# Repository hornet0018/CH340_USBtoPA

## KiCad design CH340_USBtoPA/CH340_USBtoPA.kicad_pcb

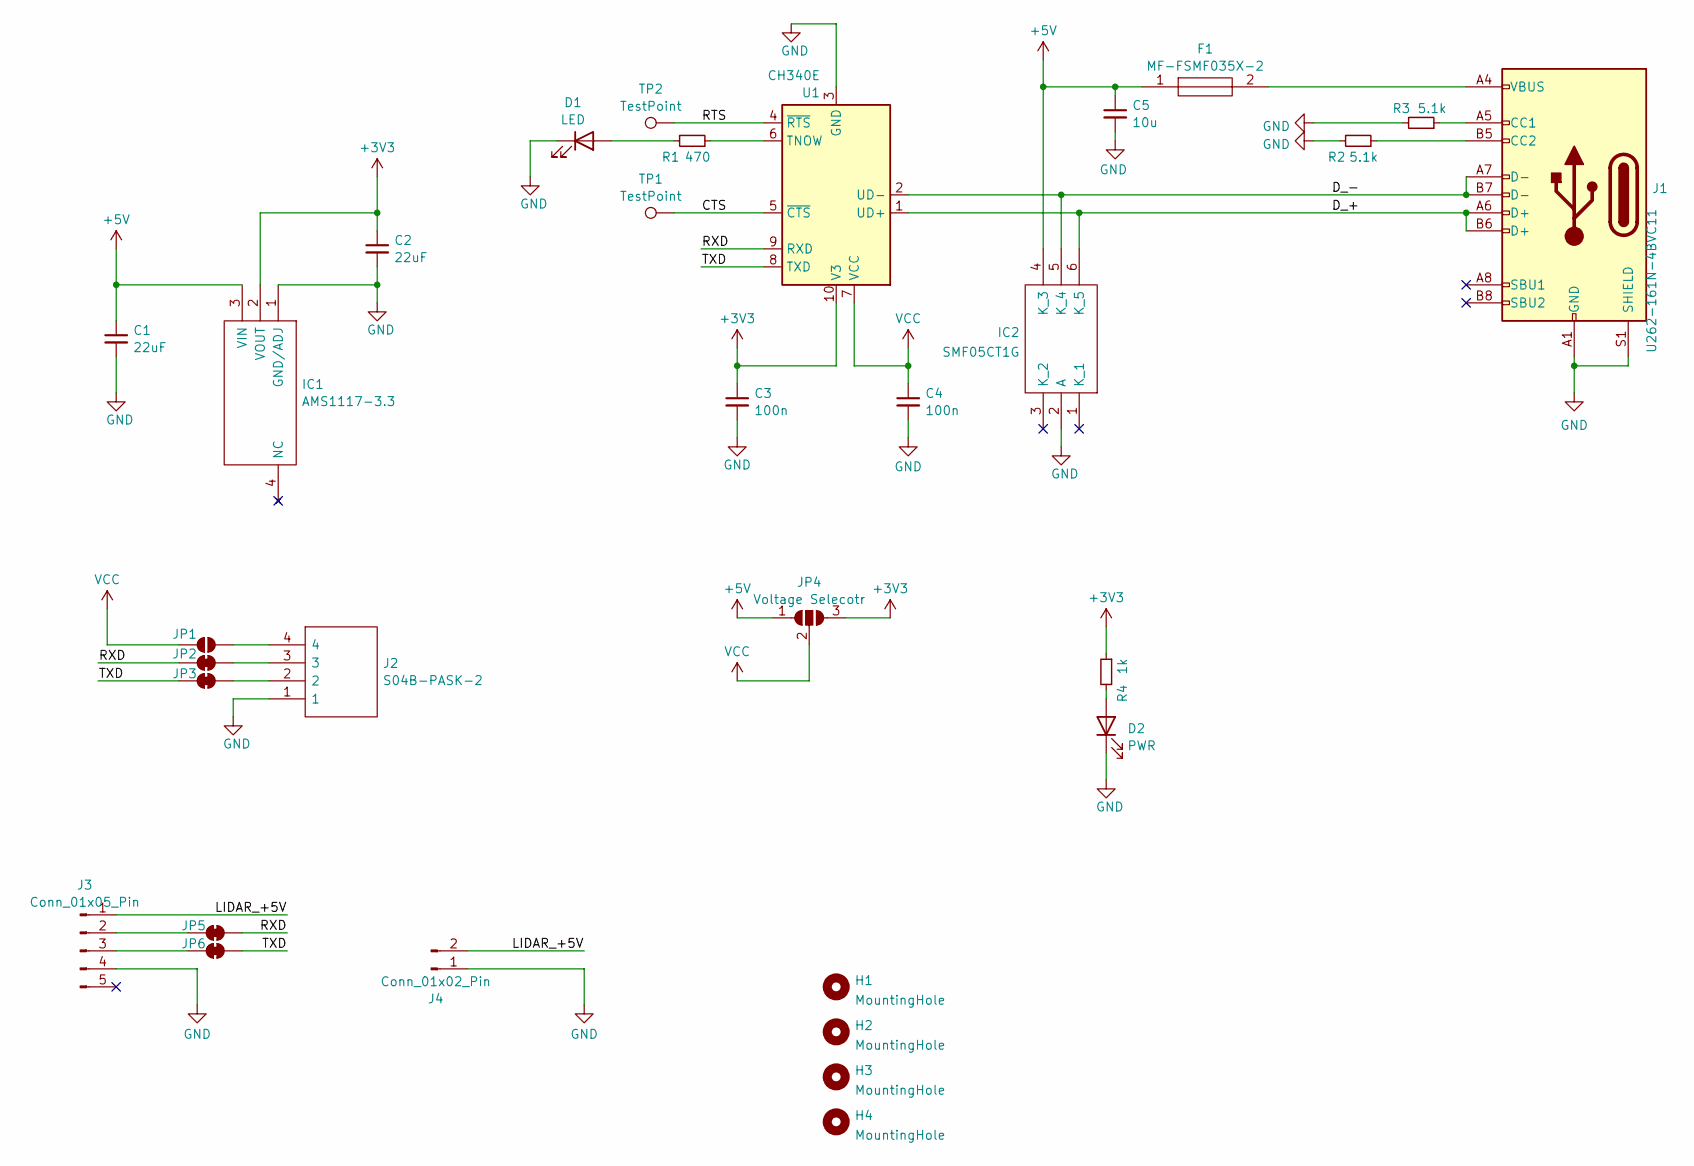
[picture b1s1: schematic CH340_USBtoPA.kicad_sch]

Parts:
C1, C2: 22uF; C_0603_1608Metric_Pad1.08x0.95mm_HandSolder
C3, C4: 100n; C_0603_1608Metric_Pad1.08x0.95mm_HandSolder
C5: 10u; C_0603_1608Metric_Pad1.08x0.95mm_HandSolder
D1: LED; LED_0603_1608Metric_Pad1.05x0.95mm_HandSolder
D2: PWR; LED_0603_1608Metric_Pad1.05x0.95mm_HandSolder
F1: MF-FSMF035X-2; FUSC1608X65N; Manufacturer_Part_Number MF-FSMF035X-2; Mouser Part Number 652-MFFSMF035X-2
H1, H2, H3, H4: MountingHole; MountingHole_3.2mm_M3_Pad_Via
IC1: AMS1117-3.3; SOT229P700X180-4N; Manufacturer_Part_Number AMS1117-3.3
IC2: SMF05CT1G; SOT65P210X110-6N; Manufacturer_Part_Number SMF05CT1G; Mouser Part Number 863-SMF05CT1G
J1: U262-161N-4BVC11; U262-16XN-4BVC11
J2: S04B-PASK-2; S04BPASK2; Manufacturer_Part_Number S04B-PASK-2
J3: Conn_01x05_Pin; JST_XH_B5B-XH-A_1x05_P2.50mm_Vertical
J4: Conn_01x02_Pin; B02BPASK1LFSN
JP1: SolderJumper_2_Open; SolderJumper-2_P1.3mm_Open_RoundedPad1.0x1.5mm
JP2, JP3, JP5, JP6: SolderJumper_2_Bridged; SolderJumper-2_P1.3mm_Bridged_RoundedPad1.0x1.5mm
JP4: Voltage Selecotr; SolderJumper-3_P1.3mm_Open_RoundedPad1.0x1.5mm
R1: 470; R_0603_1608Metric_Pad0.98x0.95mm_HandSolder
R2, R3: 5.1k; R_0603_1608Metric_Pad0.98x0.95mm_HandSolder
R4: 1k; R_0603_1608Metric_Pad0.98x0.95mm_HandSolder
TP1, TP2: TestPoint; TestPoint_Pad_D1.5mm
U1: CH340E; MSOP-10_3x3mm_P0.5mm

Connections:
+3V3: C2.1, C3.1, IC1.2 (VOUT), JP4.3 (B), R4.1, U1.10 (V3)
+5V: C1.1, C5.1, F1.1, IC1.3 (VIN), IC2.4 (K_3), JP4.1 (A)
/CTS: TP1.1, U1.5 (~CTS)
/D_+: IC2.6 (K_5), J1.A6 (D+), J1.B6 (D+), U1.1 (UD+)
/D_-: IC2.5 (K_4), J1.A7 (D-), J1.B7 (D-), U1.2 (UD-)
/LIDAR_+5V: J3.1, J4.2
/RTS: TP2.1, U1.4 (~RTS)
/RXD: JP2.1 (A), JP5.2 (B), U1.9 (RXD)
/TXD: JP3.1 (A), JP6.2 (B), U1.8 (TXD)
GND: C1.2, C2.2, C3.2, C4.2, C5.2, D1.1 (K), D2.1 (K), IC1.1 (GND/ADJ), IC2.2 (A), J1.A1 (GND), J1.A12 (GND), J1.B1 (GND), J1.B12 (GND), J1.S1 (SHIELD), J2.1, J3.4, J4.1, R2.2, R3.2, U1.3 (GND)
unnamed: D1.2 (A), R1.2
unnamed: D2.2 (A), R4.2
unnamed: F1.2, J1.A4 (VBUS), J1.A9 (VBUS), J1.B4 (VBUS), J1.B9 (VBUS)
unnamed: J1.A5 (CC1), R3.1
unnamed: J1.B5 (CC2), R2.1
unnamed: J3.2, JP5.1 (A)
unnamed: J3.3, JP6.1 (A)
unnamed: J2.4, JP1.2 (B)
unnamed: J2.3, JP2.2 (B)
unnamed: J2.2, JP3.2 (B)
unnamed: R1.1, U1.6 (TNOW)
VCC: C4.1, JP1.1 (A), JP4.2 (C), U1.7 (VCC)

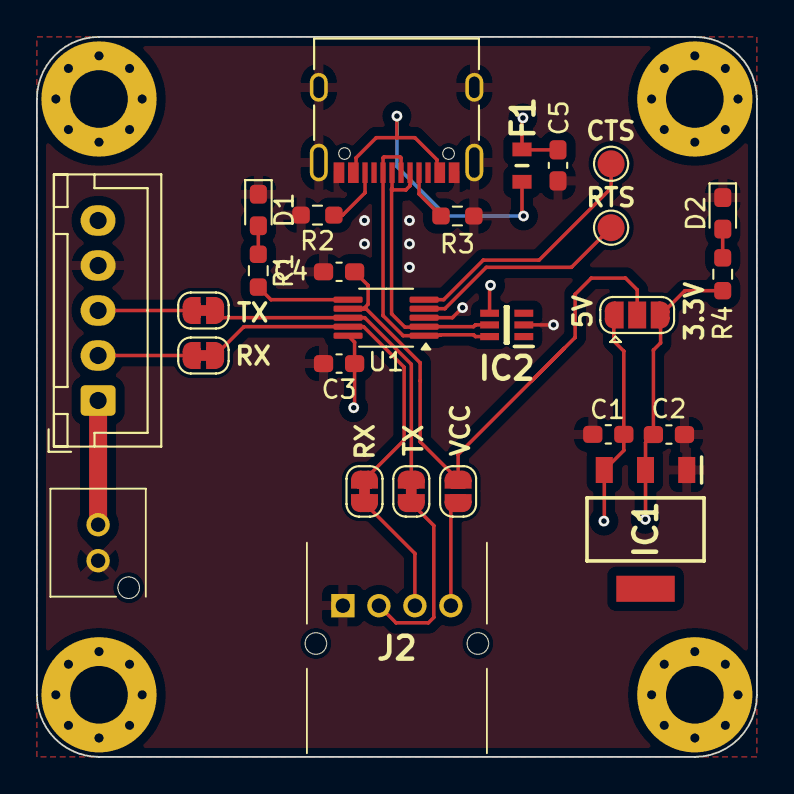
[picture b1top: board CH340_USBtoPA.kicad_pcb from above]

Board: 6 copper layers, 40.0 x 40.0 mm, 31 parts (0 on the bottom side), 22 nets.
